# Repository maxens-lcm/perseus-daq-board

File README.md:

# PERSEUS DAQ Board
<div style="display:flex; width:100%;"></div>

Carte electronique d'acquisition de donnees pour le programme fusees etudiantes PERSEUS du CNES.

Le role de cette carte est de s'interfacer avec l'OBC de la fusee, de mesurer l'environnement embarque, de stocker les donnees localement sur carte SD et de renvoyer les donnees utiles sur les bus serie de bord pour la prise de decision.

## Architecture

La carte est autonome cote alimentation et protection :

- entree depuis le bus courant de l'OBC
- protections surtension, sous-tension et surintensite
- regulation locale 3.3 V pour l'electronique embarquee
- conversion UART vers RS422 ou RS485 selon les interfaces

Coeur fonctionnel :

- SensorTile SMD au centre de la carte
- capteurs MEMS via le firmware ST `FP-SNS-ALLMEMS1`
- fusion inertielle MotionFX
- logging SD conserve
- BLE conserve pour debug/validation avec ST BLE Sensor
- sortie UART SensorTile vers transceiver RS422/RS485 pour l'OBC

GNSS :

- u-blox MAX-M10S integre sur la carte
- connecteur SMA pour l'antenne du MAX-M10S
- interface pour GNSS externe Septentrio mosaic-X5
- SUB-D 9 pour commandes UART du mosaic-X5
- canal serie dedie pour que l'OBC dialogue avec le MAX-M10S ou le mosaic-X5 via conversion RS422/UART

## Organisation du depot

```text
hardware/kicad/
  Projet KiCad de la carte PERSEUS DAQ Board.

firmware/sensortile-allmems1-uart-fusion/
  Overlay firmware pour FP-SNS-ALLMEMS1 sur SensorTile.
  Ajoute une sortie UART de trames fusion/quaternion, destinee a un convertisseur UART -> RS422.

docs/
  Synoptique systeme et documents projet.

references/obc/
  Fichiers et documents de reference lies a l'OBC PERSEUS.
```

## Firmware SensorTile

Le firmware modifie part du projet ST :

```text
fp-sns-allmems1/Projects/STM32L476JG-SensorTile/Applications/ALLMEMS1
```

Objectif firmware :

- BLE actif
- logging SD actif
- capteurs ALLMEMS1 conserves
- MotionFX actif
- USB CDC debug desactive si conflit de pins avec l'UART
- sortie UART ajoutee pour diffuser les quaternions

Important : la SensorTile ne sort pas directement du RS422. Elle sort un UART logique. La conversion vers RS422/RS485 est faite par les transceivers de la carte.

Voir [firmware/sensortile-allmems1-uart-fusion/README.md](firmware/sensortile-allmems1-uart-fusion/README.md).

## Synoptique

## Nom du repo

Nom recommande pour GitHub :

```text
perseus-daq-board
```

L'ancien nom `sequenceur_perseus` ne correspond plus au role actuel de la carte.

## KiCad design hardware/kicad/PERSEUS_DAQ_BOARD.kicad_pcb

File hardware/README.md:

# Hardware – PERSEUS DAQ Board

KiCad design files for the PERSEUS DAQ Board.

Main project:

```text
hardware/kicad/PERSEUS_DAQ_BOARD.kicad_pro
```

Main functions:

- protected power input from the OBC current bus
- local 3.3 V regulation
- SensorTile SMD integration
- MAX‑M10S GNSS integration with SMA antenna connector
- external mosaic‑X5 GNSS interface
- SD card interface
- UART to RS422/RS485 conversion channels
- SUB‑D 9 connectors for OBC and GNSS serial links

## 📂 Contenu du répertoire `hardware`

- **OBC_EXT_PCB.pdf** – schéma du PCB principal.
- **OBC_EXT_Schéma.pdf** – schéma électrique détaillé.
- **images/** – répertoire contenant les rendus et schémas d’illustration.
- **README.md** – ce fichier.

### 📋 Tables de brochage

#### J4 – RS‑422 voie 1

| Broche | Fonction |
|--------|----------|
| 1 | GND, optionnel, via R21 0 Ω |
| 2 | TX1+ |
| 3 | GND |
| 4 | RX1+ |
| 5 | +3V3, optionnel, via R18 0 Ω |
| 6 | GND, optionnel, via R20 0 Ω |
| 7 | TX1− |
| 8 | RX1− |
| 9 | GND, optionnel, via R19 0 Ω |
| **Blindage** | Shield1, relié au GND par FB2 |

#### J5 – RS‑485 / RS‑422 voie 2

| Broche | Fonction |
|--------|----------|
| 1 | GND, optionnel, via R25 0 Ω |
| 2 | TX2+ |
| 3 | GND |
| 4 | RX2+ |
| 5 | +3V3, optionnel, via R22 0 Ω |
| 6 | GND, optionnel, via R24 0 Ω |
| 7 | TX2− |
| 8 | RX2− |
| 9 | GND, optionnel, via R23 0 Ω |
| **Blindage** | Shield2, relié au GND par FB3 |

#### J6 – GNSS Mosaic‑go X5

| Broche | Fonction |
|--------|----------|
| 1 | +3V3 |
| 2 | RX2X5 – réception UART vers la carte |
| 3 | TX2X5 – émission UART depuis la carte |
| 4 | X5_TIMEPULSE |
| 5 | GND |
| 6 | GND |
| 7 | GND |
| 8 | GND |
| 9 | X5_EXTINT |
| **Blindage** | Shield3, relié au GND par FB4 |

#### J7 – GPIO, SensorTile et GNSS

| Broche | Fonction |
|--------|----------|
| 1 | GND |
| 2 | GNSS_EXTINT |
| 3 | GND |
| 4 | SENSORTILE_SCL |
| 5 | GND |
| 6 | GNSS_NRST |
| 7 | GNSS_TIMEPULSE |
| 8 | SENSORTILE_NRST |
| 9 | SENSORTILE_SDA |
| **Blindage** | Shield4, relié au GND par FB5 |

#### J9 – Alimentation batterie 24 V

| Broche | Fonction |
|--------|----------|
| 1 | Bat_24V+ |
| 2 | Bat_24V+ |
| 3 | Non connecté |
| 4 | Bat_24V− |
| 5 | Bat_24V− |
| 6 | Bat_24V+ |
| 7 | Non connecté |
| 8 | Non connecté |
| 9 | Bat_24V− |
| **Blindage** | Relié au GND par FB1 |

### 📐 Mapping des signaux différentiels (J4 & J5)

| Signal | Broche |
|--------|--------|
| RX+ | 4 |
| RX− | 8 |
| TX+ | 2 |
| TX− | 7 |
| GND principal | 3 |

Les autres broches sont des options d’alimentation ou de masse configurables par résistances 0 Ω.

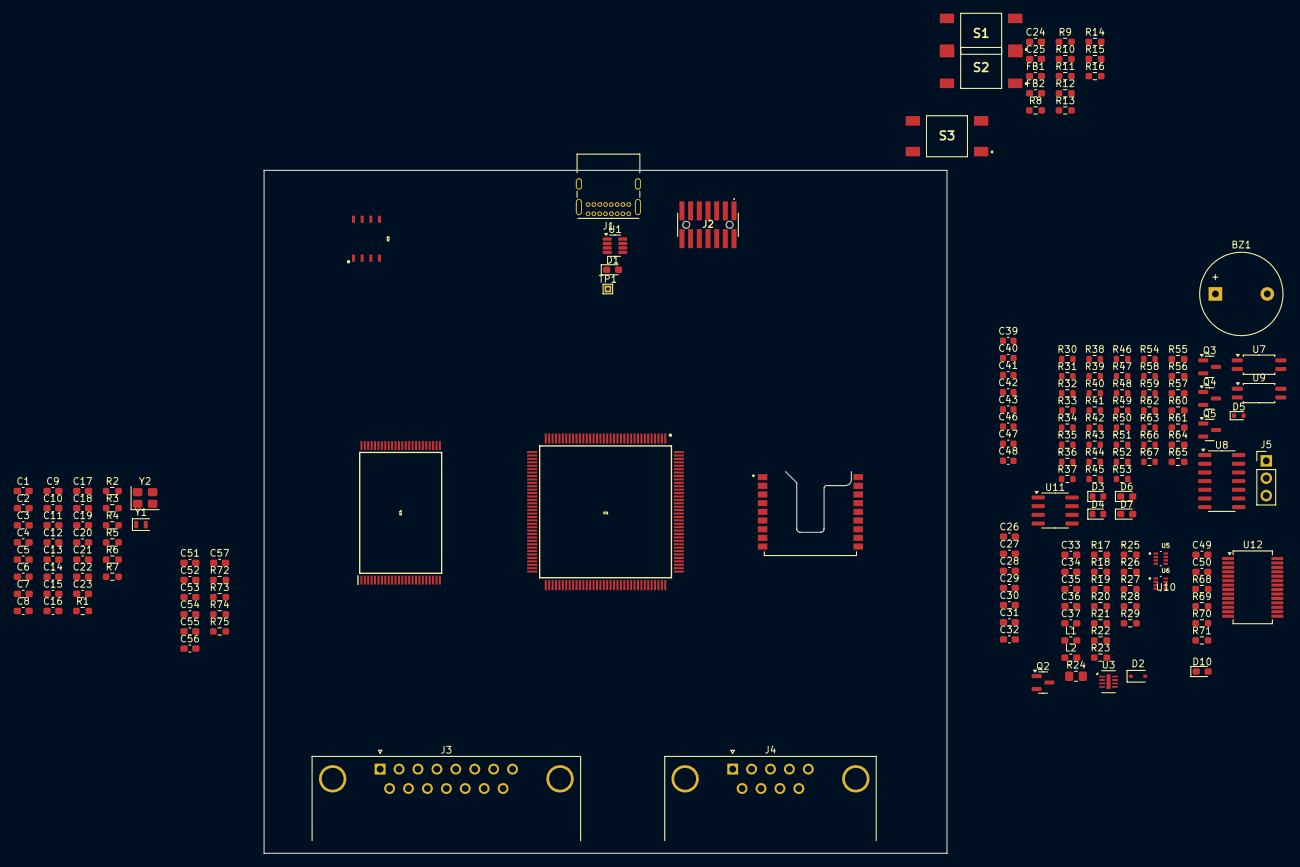
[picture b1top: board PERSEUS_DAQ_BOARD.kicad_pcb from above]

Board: 2 copper layers, 100.0 x 100.0 mm, 170 parts (0 on the bottom side), 134 nets, no tracks yet.

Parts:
BZ1: Buzzer; Buzzer_12x9.5RM7.6
C1, C5, C8, C10, C11, C12, C14, C17, C18, C19, C21, C23, C25, C26, C27, C32, C33, C49, C50, C51, C53, C56, C57: 100nF; C_0603_1608Metric_Pad1.08x0.95mm_HandSolder
C2, C3: 2.2µF; C_0603_1608Metric_Pad1.08x0.95mm_HandSolder
C4, C52, C54, C55: 10µF; C_0603_1608Metric_Pad1.08x0.95mm_HandSolder
C6, C7, C15: 1µF; C_0603_1608Metric_Pad1.08x0.95mm_HandSolder
C9: 10nF; C_0603_1608Metric_Pad1.08x0.95mm_HandSolder
C13, C16: 4pF; C_0603_1608Metric_Pad1.08x0.95mm_HandSolder
C20, C22: 8pF; C_0603_1608Metric_Pad1.08x0.95mm_HandSolder
C24: 4.7µF; C_0603_1608Metric_Pad1.08x0.95mm_HandSolder
C28, C29: 10uF; C_0603_1608Metric_Pad1.08x0.95mm_HandSolder
C30, C31: 33nF; C_0603_1608Metric_Pad1.08x0.95mm_HandSolder
C34, C35, C36, C37: 47uF; C_0603_1608Metric_Pad1.08x0.95mm_HandSolder
C39, C40, C41, C42, C43: 1uF; C_0603_1608Metric
C46, C47, C48: 100nF; C_0603_1608Metric
D1: VBUS OK; LED_0603_1608Metric_Pad1.05x0.95mm_HandSolder
D2: 1N4148WS; D_SOD-323
D3, D4: LED-R; LED_0603_1608Metric
D5: 1N4148WT; D_SOD-523
D6, D7: LED_Small; LED_0603_1608Metric_Pad1.05x0.95mm_HandSolder
D10: VBUS protection; D_0603_1608Metric_Pad1.05x0.95mm_HandSolder
FB1, FB2: BLM18KG601SN1D; L_0603_1608Metric_Pad1.05x0.95mm_HandSolder
IC1: STM32H753ZIT6; QFP50P2200X2200X160-144N
IC3: M30082040054X0IWAY; SON127P600X500X80-9N-D
IC4: MT29F8G08ADAFAWP-AAT_F; SOP50P2000X120-48N
J1: USB_C_Receptacle_USB2.0_16P; USB_C_Receptacle_GCT_USB4085
J2: FTSH-107-01-L-DV-K-A; FTSH-107-XX-YYY-DV-K-A
J3: DA15_Pins_MountingHoles; DSUB-15_Pins_Horizontal_P2.77x2.84mm_EdgePinOffset7.70mm_Ho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
J4: DE9_Pins_MountingHoles; DSUB-9_Pins_Horizontal_P2.77x2.84mm_EdgePinOffset7.70mm_Hou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
J5: Conn_01x03; PinHeader_1x03_P2.54mm_Vertical
L1, L2: L; L_0603_1608Metric_Pad1.05x0.95mm_HandSolder
Q2, Q3, Q4, Q5: BSS138; SOT-23
R1, R3, R4, R11, R72, R73, R74: 10kR; R_0603_1608Metric_Pad0.98x0.95mm_HandSolder
R2, R10, R16: NC; R_0603_1608Metric_Pad0.98x0.95mm_HandSolder
R5, R6, R14, R15, R55, R56, R60, R61: 0R; R_0603_1608Metric_Pad0.98x0.95mm_HandSolder
R7: 47R; R_0603_1608Metric_Pad0.98x0.95mm_HandSolder
R8, R9: 5kR1; R_0603_1608Metric_Pad0.98x0.95mm_HandSolder
R12: 1MR; R_0603_1608Metric_Pad0.98x0.95mm_HandSolder
R13, R64, R65: 270R; R_0603_1608Metric_Pad0.98x0.95mm_HandSolder
R17: 11M22; R_0603_1608Metric_Pad0.98x0.95mm_HandSolder
R18, R20: 100k; R_0603_1608Metric_Pad0.98x0.95mm_HandSolder
R19: 200k; R_0603_1608Metric_Pad0.98x0.95mm_HandSolder
R21, R23: 0; R_0603_1608Metric_Pad0.98x0.95mm_HandSolder
R22, R25, R27, R29, R57: 10k; R_0603_1608Metric_Pad0.98x0.95mm_HandSolder
R24: 240; R_0805_2012Metric_Pad1.20x1.40mm_HandSolder
R26: 31k; R_0603_1608Metric_Pad0.98x0.95mm_HandSolder
R28: 52.5k; R_0603_1608Metric_Pad0.98x0.95mm_HandSolder
R30, R32, R33, R34, R35, R36, R38, R39, R40, R41, R42, R43: 10K; R_0603_1608Metric
R31, R46: 470R; R_0603_1608Metric
R37, R51: 1k; R_0603_1608Metric
R44, R45, R47, R48, R49, R50, R52, R53, R58, R59, R66, R67: 0R; R_0603_1608Metric
R54: 10k; R_0603_1608Metric
R62, R63: 0R(NC); R_0603_1608Metric
R68, R69, R70: 180R; R_0603_1608Metric_Pad0.98x0.95mm_HandSolder
R71: 4.7kR; R_0603_1608Metric_Pad0.98x0.95mm_HandSolder
R75: 22R; R_0603_1608Metric_Pad0.98x0.95mm_HandSolder
S1, S2, S3: 1301.9314; 13019319
TP1: VBUS; TestPoint_THTPad_1.0x1.0mm_Drill0.5mm
U1: TCAN332G; TSOT-23-8
U3: LTC4365DDB; DFN-8-1EP_2x3mm_P0.5mm_EP0.61x2.2mm
U5, U6: TPS62933DRLR; SOTFL50P160X60-8N
U7, U9: ACPL-214-500E; SOP-4_4.4x2.6mm_P1.27mm
U8: 74HC14; SOIC-14_3.9x8.7mm_P1.27mm
U10: STEVAL-STLCS01V1; MODULE_STEVAL-STLCS01V1
U11: ADuM1281; SOIC-8_3.9x4.9mm_P1.27mm
U12: MCP23017_SO; SSOP-28_5.3x10.2mm_P0.65mm
Y1: LSE; Crystal_SMD_2012-2Pin_2.0x1.2mm
Y2: HSE; Crystal_SMD_3225-4Pin_3.2x2.5mm

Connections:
+3.3V: C25.1, C46.1, C48.1, R30.1, R32.1, R33.1, R34.1, R35.1, R36.1, R62.2, U8.14 (VCC), U11.8 (VDD2)
+3.3V-EXT: C47.1, R62.1, U11.1 (VDD1)
+3V3: C4.1, C5.1, C6.1, C7.1, C8.1, C9.1, C10.1, C11.1, C12.1, C14.1, C18.1, C19.1, C21.1, C23.1, C35.2, C37.2, C49.1, C51.1, C52.1, C54.1, C55.1, C56.1, C57.1, IC1.6 (VBAT), IC1.17 (VDD_1), IC1.30 (VDD_2), IC1.33 (VDDA), IC1.39 (VDD_3), IC1.52 (VDD_4), IC1.62 (VDD_5), IC1.72 (VDD_6), IC1.84 (VDD_7), IC1.95 (VDD33_USB), IC1.108 (VDD_8), IC1.121 (VDD_9), IC1.131 (VDD_10), IC1.144 (VDD_11), IC3.8 (VCC), IC4.12 (VCC_1), IC4.37 (VCC_2), J2.3, L2.2, R1.1, R7.1, R26.1, R57.2, R64.1, R65.1, R71.1, R72.1, R73.1, R74.2, S3.3 (COM_1), U1.3 (VCC), U10.3 (VIN), U12.9 (VDD)
+5V: BZ1.1 (+), C34.2, C36.2, D5.1 (K), L1.2, R28.1
/CONNECTORS/Bat_24V+: D2.2 (A), J4.9, R17.2, R20.2, U3.4 (Vin)
/CONNECTORS/JTDI: IC1.110 (PA15), J2.10
/CONNECTORS/NJTRST: IC1.134 (PB4), J2.12
/CONNECTORS/SWCLK_JTCK: IC1.109 (PA14), J2.6
/CONNECTORS/SWDIO_JTMS: IC1.105 (PA13), J2.4
/CONNECTORS/SWO_JTDO: IC1.133 (PB3), J2.8
/CONNECTORS/UART_DEBUG_RX: IC1.70 (PB11), J2.13
/CONNECTORS/UART_DEBUG_TX: IC1.69 (PB10), J2.14
/CONNECTORS/USB_CONN_D+: J1.A6 (D+), J1.B6 (D+)
/CONNECTORS/USB_CONN_D-: J1.A7 (D-), J1.B7 (D-)
/CONNECTORS/VBUS_SENSING: IC1.101 (PA9), R13.1
/EXTENDEUR_GPIO/I2C_2_SCL: IC1.11 (PF1), U12.12 (SCK)
/EXTENDEUR_GPIO/I2C_2_SDA: IC1.10 (PF0), U12.13 (SDA)
/EXTENDEUR_GPIO/INTA_MCP: IC1.78 (PD9), U12.20 (INTA)
/EXTENDEUR_GPIO/INTB_MCP: IC1.77 (PD8), U12.19 (INTB)
/EXTENDEUR_GPIO/LED_BLUE: IC1.45 (PC5), R68.2
/EXTENDEUR_GPIO/LED_GREEN: IC1.47 (PB1), R69.1
/EXTENDEUR_GPIO/LED_RED: IC1.46 (PB0), R70.1
/EXTENDEUR_GPIO/MCPRST: C50.1, IC1.13 (PF3), IC1.66 (PE13), R71.2, U12.18 (~RESET)
/MCU/5V_EN: IC1.116 (PD2), R25.1, U5.2 (EN)
/MCU/BUZZ: IC1.41 (PA5), Q3.1 (G), R54.2
/MCU/FLASH_ALE: IC1.81 (PD12), IC4.17 (ALE)
/MCU/FLASH_CLE: IC1.80 (PD11), IC4.16 (CLE)
/MCU/FLASH_IO0: IC1.85 (PD14), IC4.29 (I/O0)
/MCU/FLASH_IO1: IC1.86 (PD15), IC4.30 (I/O1)
/MCU/FLASH_IO2: IC1.114 (PD0), IC4.31 (I/O2)
/MCU/FLASH_IO3: IC1.115 (PD1), IC4.32 (I/O3)
/MCU/FLASH_IO4: IC1.58 (PE7), IC4.41 (I/O4)
/MCU/FLASH_IO5: IC1.59 (PE8), IC4.42 (I/O5)
/MCU/FLASH_IO6: IC1.60 (PE9), IC4.43 (I/O6)
/MCU/FLASH_IO7: IC1.63 (PE10), IC4.44 (I/O7)
/MCU/FLASH_NCE: IC1.98 (PC8), IC4.9 (CE#), R72.2
/MCU/FLASH_NRE: IC1.118 (PD4), IC4.8 (RE#)
/MCU/FLASH_NR/B: IC4.7 (R/B#), R5.2, R6.2, R73.2
/MCU/FLASH_NWE: IC1.119 (PD5), IC4.18 (WE#)
/MCU/FLASH_NWP: C53.1, IC1.79 (PD10), IC4.19 (WP#), R74.1
/MCU/HSE_IN: C20.1, IC1.23 (PH0-OSC_IN), Y2.1
/MCU/HSE_OUT: C22.1, IC1.24 (PH1-OSC_OUT), Y2.3
/MCU/LSE_IN: C13.1, IC1.8 (PC14-OSC32_IN), Y1.1
/MCU/LSE_OUT: C16.1, IC1.9 (PC15-OSC32_OUT), Y1.2
/MCU/MRAM_CLK: IC1.22 (PF10), R75.2
/MCU/MRAM_IO_0: IC1.20 (PF8), IC3.5 (SI_/_IO[0])
/MCU/MRAM_IO_1: IC1.21 (PF9), IC3.2 (SO_/_IO[1])
/MCU/MRAM_IO_2: IC1.1 (PE2), IC3.3 (WP#_/_IO[2])
/MCU/MRAM_IO_3: IC1.18 (PF6), IC3.7 (IO[3])
/MCU/MRAM_NCS: IC1.91 (PG6), IC3.1 (CS#)
/MCU/NRST: C1.1, IC1.25 (NRST)
/MCU/SENSORTILE_I2C_SCL: IC1.136 (PB6), U10.13 (GPIO3)
/MCU/SENSORTILE_I2C_SDA: IC1.137 (PB7), U10.12 (GPIO2)
/MCU/SENSORTILE_NRST: IC1.36 (PA2), S2.1 (NO_1), U10.14 (NRST)
/MCU/SENSORTILE_UART_RX: IC1.35 (PA1), R55.2, R60.1
/MCU/SENSORTILE_UART_TX: IC1.34 (PA0-WKUP), R56.2, R61.1
/MCU/SPI_1_MISO: IC1.42 (PA6), IC1.124 (PG9)
/MCU/SPI_1_MOSI: IC1.43 (PA7), IC1.123 (PD7)
/MCU/VREF+: C15.1, C17.1, IC1.32 (VREF+), R7.2
/POWER/VBATT: C26.2, C27.2, C28.2, C29.2, U3.6 (Vout), U5.3 (VIN), U6.3 (VIN)
/SENSORS/IN_N1: C43.1, R36.2, R38.2
/SENSORS/IN_N2: C42.1, R35.2, R39.2
/SENSORS/IN_N3: C41.1, R34.2, R40.2
/SENSORS/IN_N4: C40.1, R33.2, R41.2
/SENSORS/IN_N5: C39.1, R32.2, R42.2
/SENSORS/IN_N6: R30.2, R43.2
/SENSORS/RXD: J5.3, R55.1, U10.6 (RXD/USB_DP)
/SENSORS/TXD: J5.2, R56.1, U10.7 (TXD/USB_DM)
GND: C1.2, C2.2, C3.2, C4.2, C5.2, C6.2, C7.2, C8.2, C9.2, C10.2, C11.2, C12.2, C13.2, C14.2, C15.2, C16.2, C17.2, C18.2, C19.2, C20.2, C21.2, C22.2, C23.2, C24.1, C25.2, C26.1, C27.1, C28.1, C29.1, C30.1, C31.1, C34.1, C35.1, C36.1, C37.1, C39.2, C40.2, C41.2, C42.2, C43.2, C46.2, C48.2, C49.2, C50.2, C51.2, C52.2, C53.2, C54.2, C55.2, C56.2, C57.2, D10.2 (A), FB1.2, FB2.2, IC1.16 (VSS_1), IC1.31 (VSSA), IC1.38 (VSS_2), IC1.51 (VSS_3), IC1.61 (VSS_4), IC1.83 (VSS_5), IC1.94 (VSS_6), IC1.107 (VSS_7), IC1.120 (VSS_8), IC1.130 (VSS_9), IC3.4 (VSS), IC4.13 (VSS_1), IC4.36 (VSS_2), IC4.38 (PRE/VSS), J1.A1 (GND), J1.A12 (GND), J1.B1 (GND), J1.B12 (GND), J2.5, J2.7, J2.11, J4.3, J4.6, J5.1, Q2.2 (S), Q3.2 (S), Q4.2 (S), Q5.2 (S), R2.1, R4.1, R8.1, R9.1, R10.2, R12.1, R16.2, R19.1, R25.2, R27.2, R29.2, R54.1, R63.2, S1.1 (NO_1), S2.3 (COM_1), U1.2 (GND), U3.1 (GND), U3.9 (GND), U5.4 (GND), U6.4 (GND), U7.2, U8.7 (GND), U9.2, U10.5 (VSS), U10.17 (GND), U10.18 (GND__1), U11.5 (GND2), U12.10 (VSS), Y2.2, Y2.4
GNDD-EXT: C47.2, R63.1, U11.4 (GND1)
unnamed: BZ1.2 (-), D5.2 (A), Q3.3 (D)
unnamed: D1.2 (A), R13.2
unnamed: D2.1 (K), R22.1
unnamed: D3.2 (A), R44.1, U7.3
unnamed: D3.1 (K), R37.1
unnamed: D4.2 (A), R53.1, U9.3
unnamed: D4.1 (K), R51.1
unnamed: D6.2 (A), R64.2
unnamed: D6.1 (K), Q4.3 (D)
unnamed: D7.2 (A), R65.2
unnamed: D7.1 (K), Q5.3 (D)
unnamed: IC1.138 (BOOT0), R3.1, R4.2
unnamed: IC1.96 (PC6), R5.1
unnamed: IC1.143 (PDR_ON), R1.2, R2.2
unnamed: IC1.92 (PG7), R6.1
unnamed: C2.1, IC1.71 (VCAP1)
unnamed: C3.1, IC1.106 (VCAP2)
unnamed: IC3.6 (CLK), R75.1
unnamed: J1.A5 (CC1), R8.2
unnamed: J1.B5 (CC2), R9.2
unnamed: R11.2, R12.2
unnamed: Q2.3 (D), R24.2
unnamed: Q2.1 (G), R23.2
unnamed: Q4.1 (G), R60.2
unnamed: Q5.1 (G), R61.2
unnamed: R31.2, U7.1
unnamed: R38.1, U8.1
unnamed: R39.1, U8.3
unnamed: R40.1, U8.5
unnamed: R41.1, U8.9
unnamed: R42.1, U8.11
unnamed: R43.1, U8.13
unnamed: R45.2, U8.2
unnamed: R46.2, U9.1
unnamed: R47.2, U8.4
unnamed: R48.2, U8.6
unnamed: R49.2, U8.8
unnamed: R50.2, U8.10
unnamed: R52.2, U8.12
unnamed: J4.7, U1.7 (CANH)
unnamed: J4.2, U1.6 (CANL)
unnamed: R15.2, U1.4 (RXD)
unnamed: R14.2, U1.1 (TXD)
unnamed: R21.1, U3.5 (GATE)
unnamed: R18.1, R19.2, U3.2 (OV)
unnamed: R17.1, R18.2, U3.3 (UV)
unnamed: R22.2, R23.1, U3.7 (~FAULT)
unnamed: R20.1, U3.8 (~SHDN)
unnamed: C32.1, U5.6 (BST)
unnamed: R28.2, R29.1, U5.8 (FB)
unnamed: C30.2, U5.7 (SS)
unnamed: C32.2, L1.1, U5.5 (SW)
unnamed: C33.1, U6.6 (BST)
unnamed: R26.2, R27.1, U6.8 (FB)
unnamed: C31.2, U6.7 (SS)
unnamed: C33.2, L2.1, U6.5 (SW)
unnamed: R57.1, U10.4 (VDDUSB)
unnamed: R66.1, U11.7 (VIA)
unnamed: R59.2, U11.3 (VIB)
unnamed: R58.2, U11.2 (VOA)
unnamed: R67.1, U11.6 (VOB)
Shield: FB1.1, J1.S1 (SHIELD), R10.1
Shield_CAN: FB2.1, J4.0 (PAD), J4.5, R16.1
VBUS_5V_USB: C24.2, D10.1 (K), J1.A4 (VBUS), J1.A9 (VBUS), J1.B4 (VBUS), J1.B9 (VBUS), R11.1, TP1.1

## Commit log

2026-06-16 Initial SensorTile UART fusion overlay
2026-06-16 Add hardware design and project documentation
2026-06-18 Add comprehensive README and update UART Fusion implementation,
2026-06-22 Add complete SensorTile firmware sources
2026-06-22 Fix visualisation rendering + document binary frame layout
2026-06-22 Add hardware PDFs, pinout image and tables to README
2026-06-22 Fix UART stall: non‑blocking SD logging and raise UART5 IRQ priority
2026-06-22 Update baudrate to 115200 and add UART transmission safety
2026-06-23 Prepare clean release: add LICENSE, requirements, changelog, improve README, fix decoder output, unify baudrate, add tests and assets
2026-06-23 Make README images full-width side-by-side
2026-06-29 Replace synoptic Draw.io with PNG
